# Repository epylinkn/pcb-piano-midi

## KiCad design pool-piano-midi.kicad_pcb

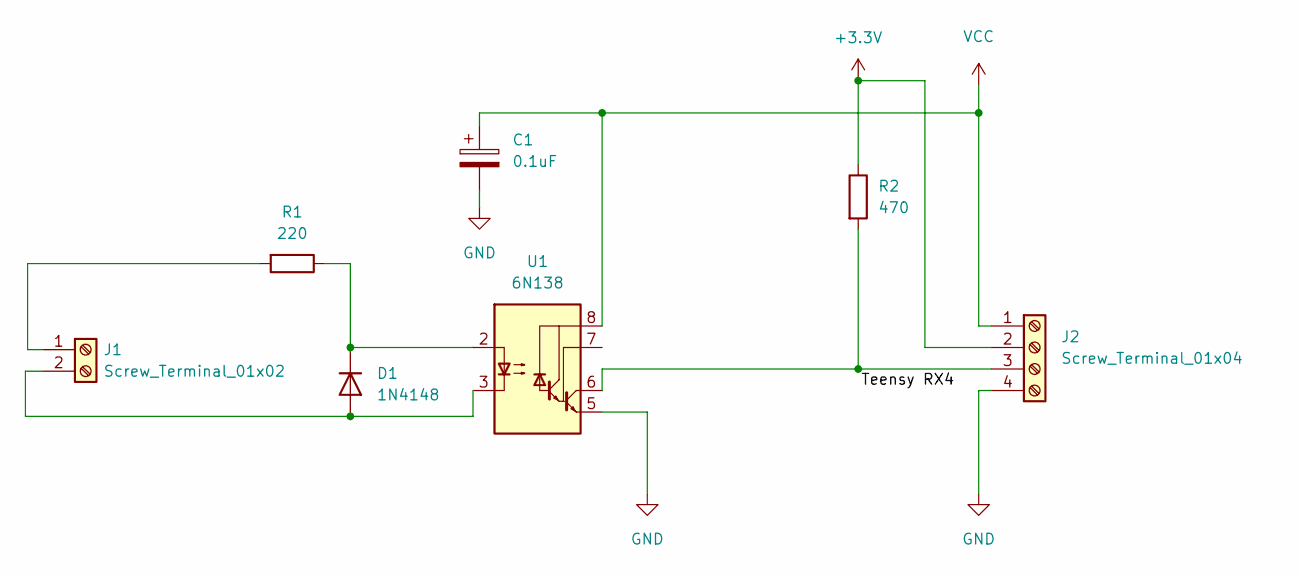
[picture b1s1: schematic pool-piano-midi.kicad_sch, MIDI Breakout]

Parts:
C1: 0.1uF; CP_Radial_Tantal_D5.5mm_P5.00mm
D1: 1N4148; D_DO-35_SOD27_P7.62mm_Horizontal
J1: Screw_Terminal_01x02; TerminalBlock_bornier-2_P5.08mm
J2: Screw_Terminal_01x04; TerminalBlock_bornier-4_P5.08mm
R1: 220; R_Axial_DIN0309_L9.0mm_D3.2mm_P12.70mm_Horizontal
R2: 470; R_Axial_DIN0309_L9.0mm_D3.2mm_P12.70mm_Horizontal
U1: 6N138; DIP-8_W7.62mm

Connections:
+3V3: J2.2, R2.1
GND: C1.2, J2.4, U1.5 (GND)
unnamed: D1.1 (K), R1.1, U1.2 (C1)
unnamed: D1.2 (A), J1.2, U1.3 (C2)
unnamed: J1.1, R1.2
unnamed: J2.3, R2.2, U1.6 (VO2)
VCC: C1.1, J2.1, U1.8 (VCC)

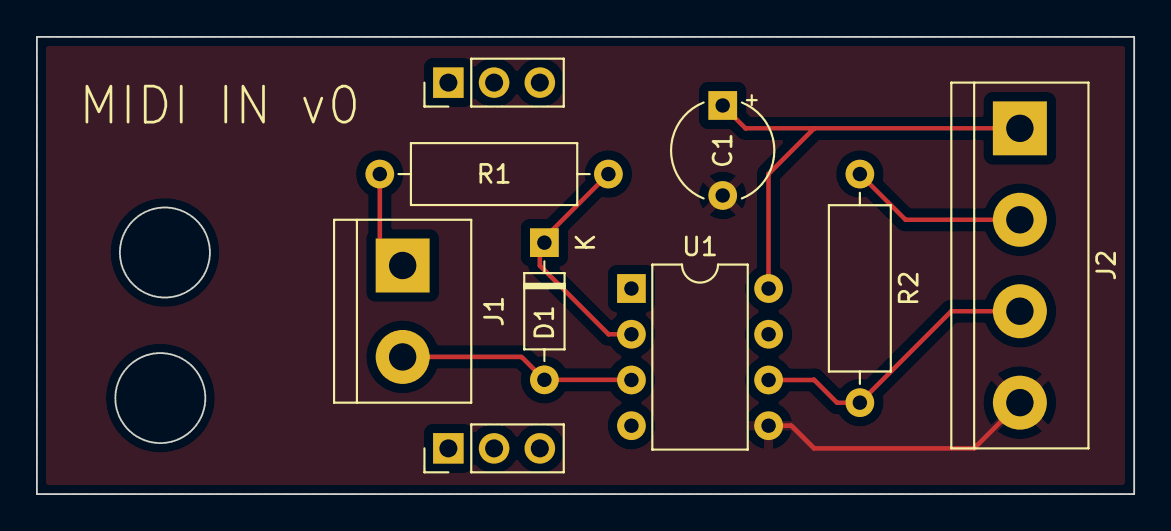
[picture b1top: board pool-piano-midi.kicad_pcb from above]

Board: 2 copper layers, 61.0 x 25.4 mm, 7 parts (0 on the bottom side), 7 nets.

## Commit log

2022-05-26 midi breakout with screw terminals
